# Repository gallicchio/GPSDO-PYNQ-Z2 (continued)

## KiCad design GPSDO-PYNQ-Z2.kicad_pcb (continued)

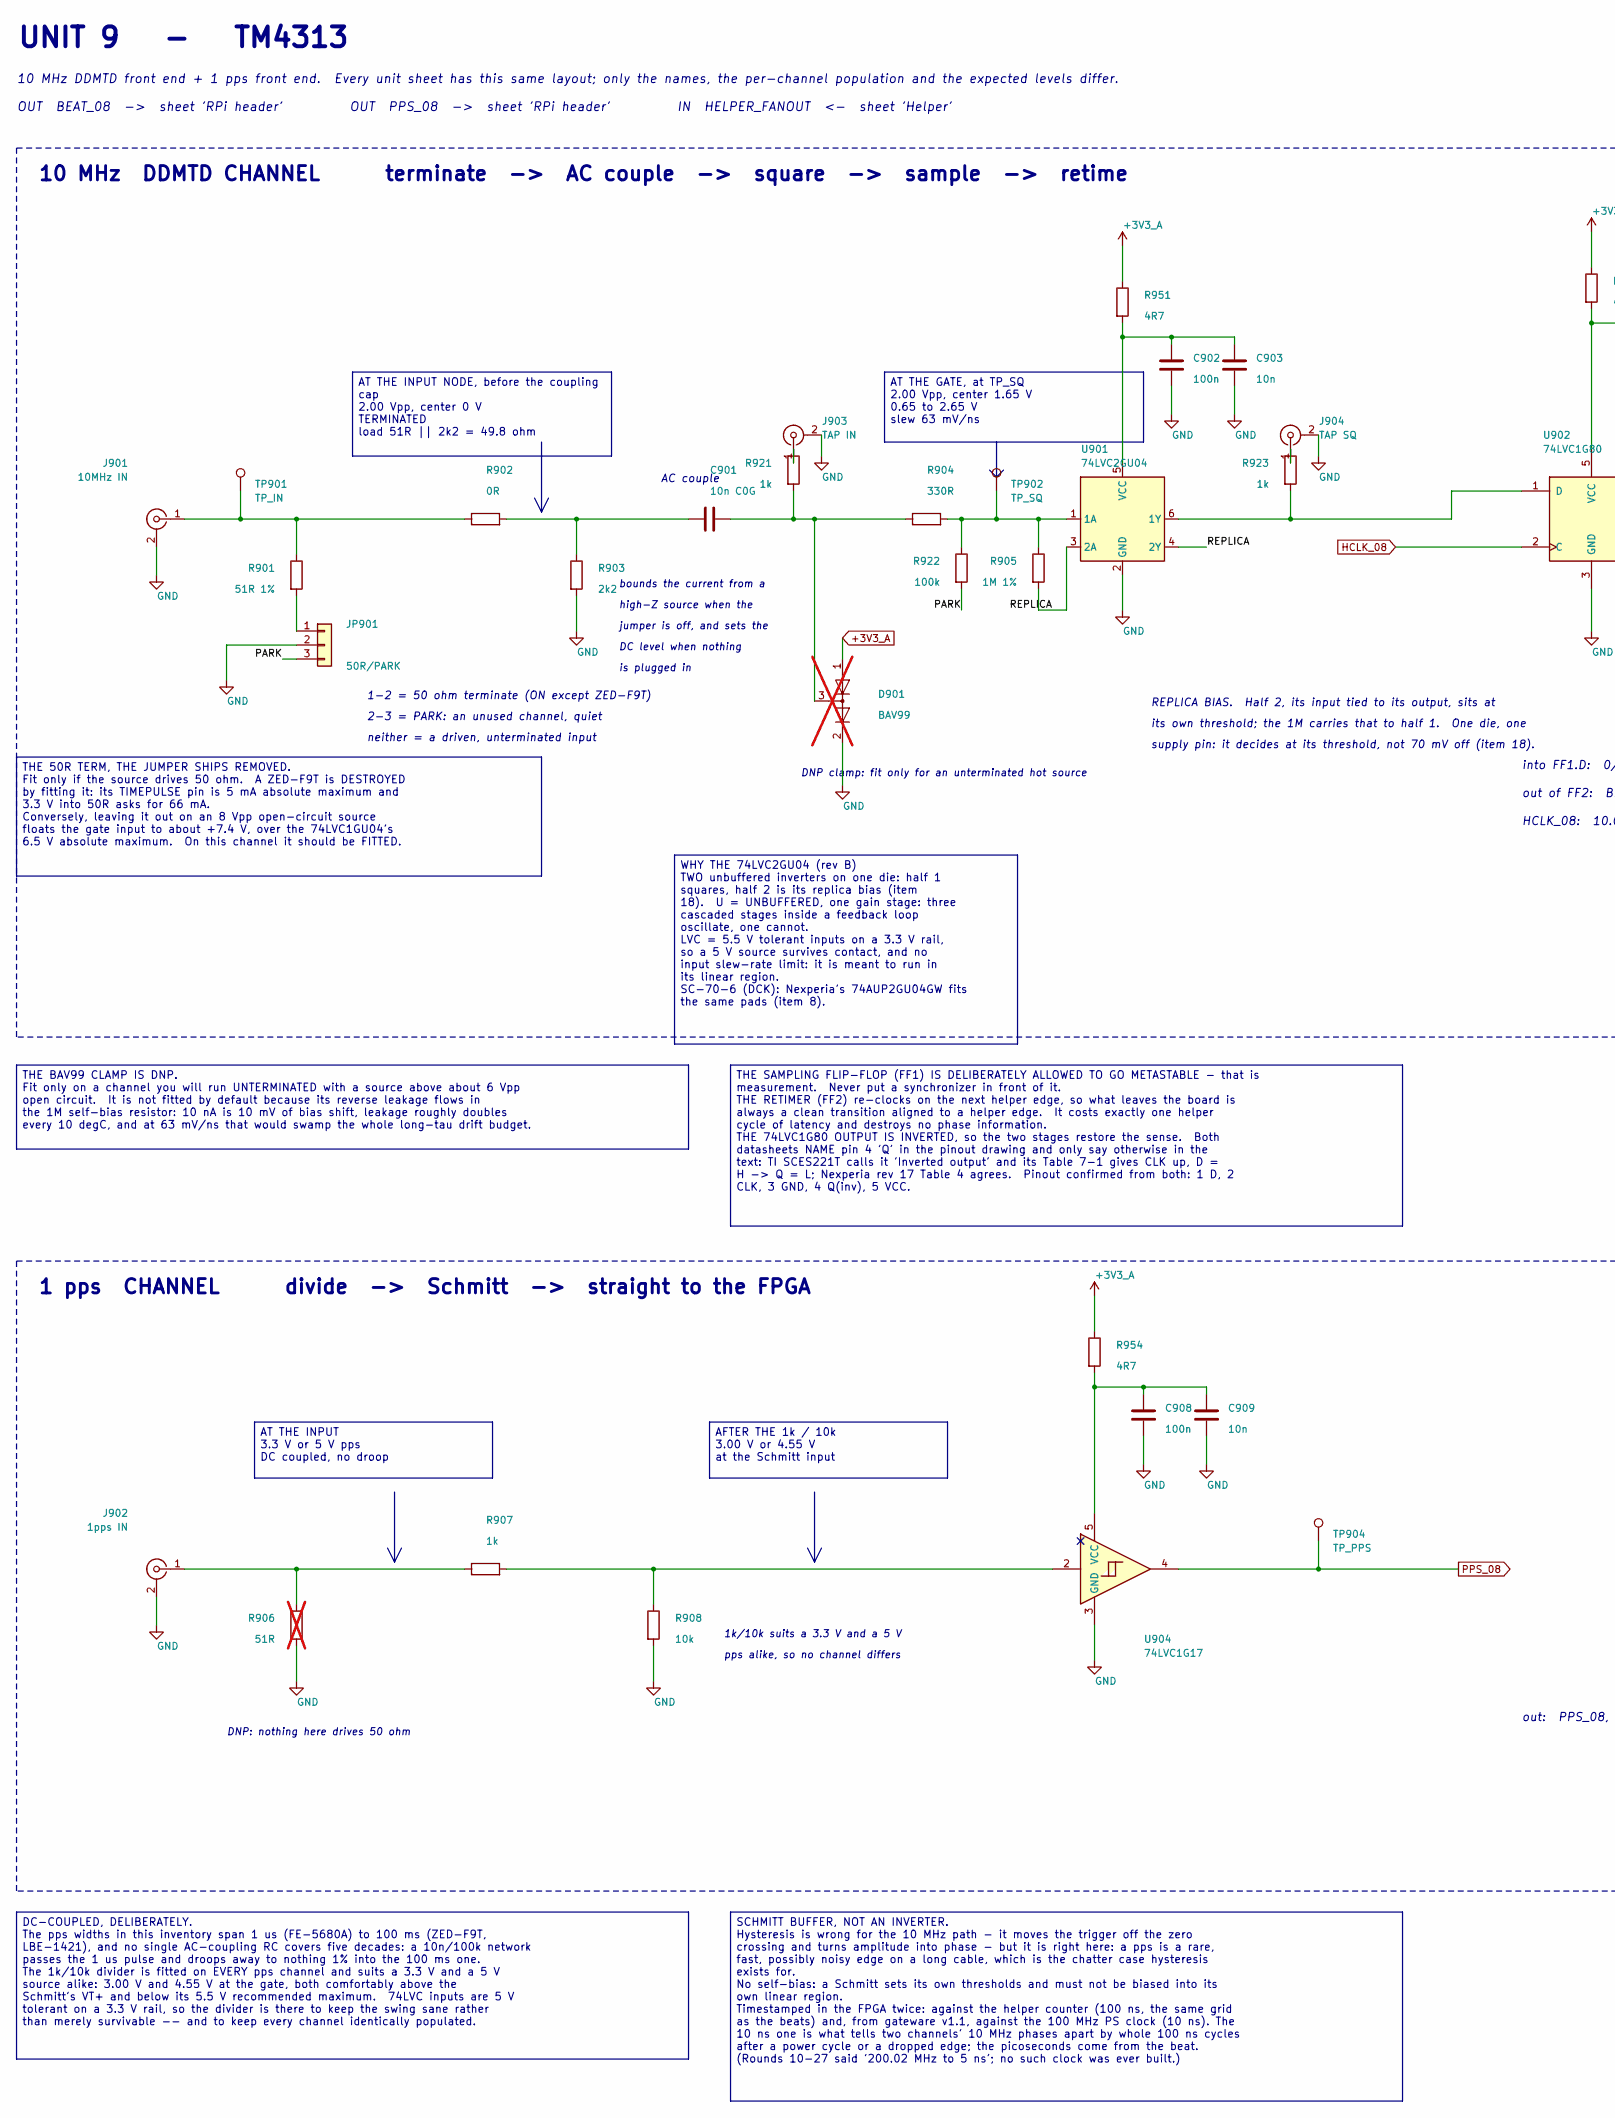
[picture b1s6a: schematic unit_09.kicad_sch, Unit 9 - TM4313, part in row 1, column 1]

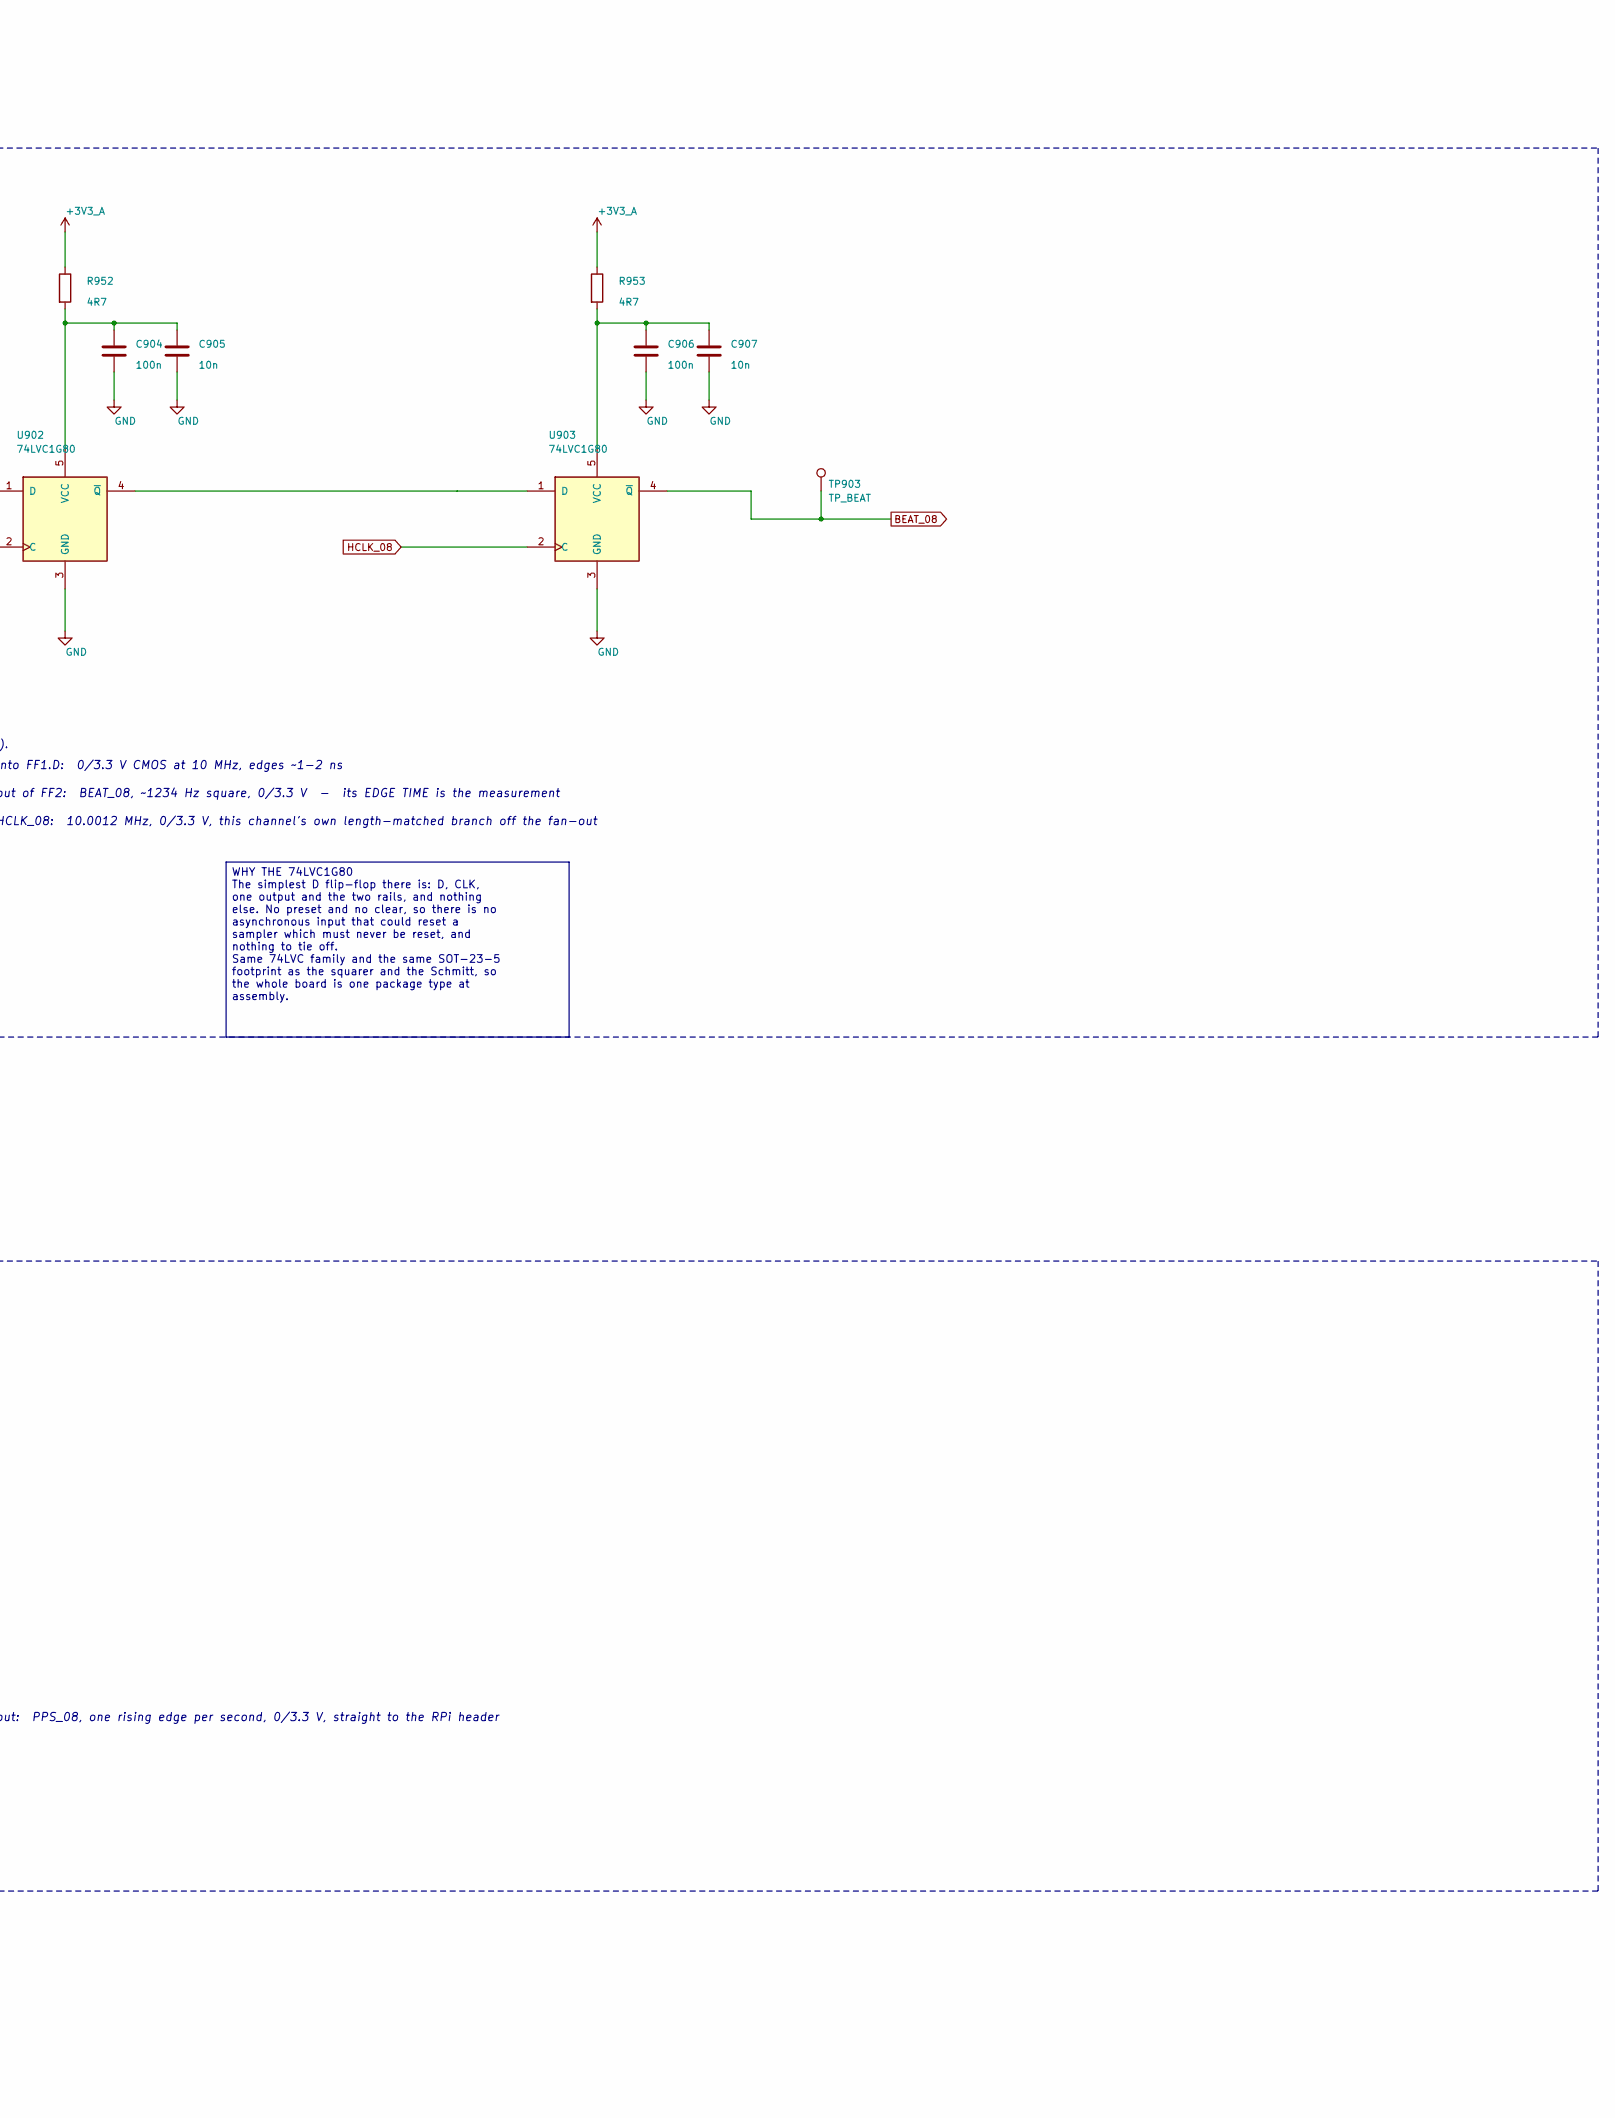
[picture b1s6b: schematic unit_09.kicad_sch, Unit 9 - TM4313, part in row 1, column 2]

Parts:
C901: 10n C0G; C_0805_2012Metric
C902, C904, C906, C908: 100n; C_0805_2012Metric
C903, C905, C907, C909: 10n; C_0805_2012Metric
D901: BAV99; SOT-23; LCSC C916421; not fitted
J901: 10MHz IN; SMA_Vertical_THT_Universal; LCSC C496549
J902: 1pps IN; SMA_Vertical_THT_Universal; LCSC C496549
J903: TAP IN; U.FL_Hirose_U.FL-R-SMT-1_Vertical; LCSC C88374
J904: TAP SQ; U.FL_Hirose_U.FL-R-SMT-1_Vertical; LCSC C88374
JP901: 50R/PARK; PinHeader_1x03_P2.54mm_Vertical
R901: 51R 1%; R_0805_2012Metric
R902: 0R; R_0805_2012Metric
R903: 2k2; R_0805_2012Metric
R904: 330R; R_0805_2012Metric
R905: 1M 1%; R_0805_2012Metric
R906: 51R; R_0805_2012Metric; not fitted
R907, R921, R923: 1k; R_0805_2012Metric
R908: 10k; R_0805_2012Metric
R922: 100k; R_0805_2012Metric
R951, R952, R953, R954: 4R7; R_0805_2012Metric
TP901: TP_IN; TestPoint_Pad_D1.5mm
TP902: TP_SQ; TestPoint_Pad_D1.5mm
TP903: TP_BEAT; TestPoint_Pad_D1.5mm
TP904: TP_PPS; TestPoint_Pad_D1.5mm
U901: 74LVC2GU04; SOT-363_SC-70-6; LCSC C116660
U902, U903: 74LVC1G80; SOT-23-5; LCSC C42879
U904: 74LVC1G17; SOT-23-5; LCSC C7836

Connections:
+3V3_A: D901.1 (K), R951.1, R952.1, R953.1, R954.1; also elsewhere on the board
/Unit 09/PARK: JP901.3, R922.2
/Unit 09/REPLICA: R905.2, U901.3 (2A), U901.4 (2Y)
BEAT_08: TP903.1, U903.4 (~Q); also elsewhere on the board
GND: C902.2, C903.2, C904.2, C905.2, C906.2, C907.2, C908.2, C909.2, D901.2 (A), J901.2 (Ext), J902.2 (Ext), J903.2 (Ext), J904.2 (Ext), JP901.2, R903.2, R906.2, R908.2, U901.2 (GND), U902.3 (GND), U903.3 (GND), U904.3 (GND); also elsewhere on the board
HCLK_08: U902.2 (C), U903.2 (C); also elsewhere on the board
unnamed: J901.1 (In), R901.1, R902.1, TP901.1
unnamed: J902.1 (In), R906.1, R907.1
unnamed: J903.1 (In), R921.1
unnamed: J904.1 (In), R923.1
unnamed: JP901.1, R901.2
unnamed: R907.2, R908.1, U904.2
unnamed: R904.2, R905.1, R922.1, TP902.1, U901.1 (1A)
unnamed: R923.2, U901.6 (1Y), U902.1 (D)
unnamed: C902.1, C903.1, R951.2, U901.5 (VCC)
unnamed: C904.1, C905.1, R952.2, U902.5 (VCC)
unnamed: U902.4 (~Q), U903.1 (D)
unnamed: C906.1, C907.1, R953.2, U903.5 (VCC)
unnamed: C908.1, C909.1, R954.2, U904.5 (VCC)
PPS_08: TP904.1, U904.4; also elsewhere on the board

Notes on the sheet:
UNIT 9 - TM4313
out of FF2: BEAT_08, ~1234 Hz square, 0/3.3 V - its EDGE TIME is the measurement
DNP: nothing here drives 50 ohm
bounds the current from a
supply pin: it decides at its threshold, not 70 mV off (item 18).
high-Z source when the
neither = a driven, unterminated input
1 pps CHANNEL divide -> Schmitt -> straight to the FPGA
is plugged in
10 MHz DDMTD front end + 1 pps front end. Every unit sheet has this same layout; only the names, the per-channel population and the expected levels differ.
pps alike, so no channel differs
OUT BEAT_08 -> sheet 'RPi header' OUT PPS_08 -> sheet 'RPi header' IN HELPER_FANOUT <- sheet 'Helper'
DNP clamp: fit only for an unterminated hot source
1-2 = 50 ohm terminate (ON except ZED-F9T)
DC level when nothing
HCLK_08: 10.0012 MHz, 0/3.3 V, this channel's own length-matched branch off the fan-out
jumper is off, and sets the
into FF1.D: 0/3.3 V CMOS at 10 MHz, edges ~1-2 ns
out: PPS_08, one rising edge per second, 0/3.3 V, straight to the RPi header
its own threshold; the 1M carries that to half 1. One die, one
1k/10k suits a 3.3 V and a 5 V
2-3 = PARK: an unused channel, quiet
AC couple
REPLICA BIAS. Half 2, its input tied to its output, sits at
10 MHz DDMTD CHANNEL terminate -> AC couple -> square -> sample -> retime
AFTER THE 1k / 10k 3.00 V or 4.55 V at the Schmitt input
THE SAMPLING FLIP-FLOP (FF1) IS DELIBERATELY ALLOWED TO GO METASTABLE - that is measurement. Never put a synchronizer in front of it. THE RETIMER (FF2) re-clocks on the next helper edge, so what leaves the board is always a clean transition aligned to a helper edge. It costs exactly one helper cycl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
AT THE INPUT 3.3 V or 5 V pps DC coupled, no droop
THE 50R TERM, THE JUMPER SHIPS REMOVED. Fit only if the source drives 50 ohm. A ZED-F9T is DESTROYED by fitting it: its TIMEPULSE pin is 5 mA absolute maximum and 3.3 V into 50R asks for 66 mA. Conversely, leaving it out on an 8 Vpp open-circuit source floats the gate input to about +7.4 V, over th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
DC-COUPLED, DELIBERATELY. The pps widths in this inventory span 1 us (FE-5680A) to 100 ms (ZED-F9T, LBE-1421), and no single AC-coupling RC covers five decades: a 10n/100k network passes the 1 us pulse and droops away to nothing 1% into the 100 ms one. The 1k/10k divider is fitted on EVERY pps chan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
WHY THE 74LVC2GU04 (rev B) TWO unbuffered inverters on one die: half 1 squares, half 2 is its replica bias (item 18). U = UNBUFFERED, one gain stage: three cascaded stages inside a feedback loop oscillate, one cannot. LVC = 5.5 V tolerant inputs on a 3.3 V rail, so a 5 V source survives contact, an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
WHY THE 74LVC1G80 The simplest D flip-flop there is: D, CLK, one output and the two rails, and nothing else. No preset and no clear, so there is no asynchronous input that could reset a sampler which must never be reset, and nothing to tie off. Same 74LVC family and the same SOT-23-5 footprint as t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
AT THE INPUT NODE, before the coupling cap 2.00 Vpp, center 0 V TERMINATED load 51R || 2k2 = 49.8 ohm
THE BAV99 CLAMP IS DNP. Fit only on a channel you will run UNTERMINATED with a source above about 6 Vpp open circuit. It is not fitted by default because its reverse leakage flows in the 1M self-bias resistor: 10 nA is 10 mV of bias shift, leakage roughly doubles every 10 degC, and at 63 mV/ns that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
SCHMITT BUFFER, NOT AN INVERTER. Hysteresis is wrong for the 10 MHz path - it moves the trigger off the zero crossing and turns amplitude into phase - but it is right here: a pps is a rare, fast, possibly noisy edge on a long cable, which is the chatter case hysteresis exists for. No self-bias: a S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
AT THE GATE, at TP_SQ 2.00 Vpp, center 1.65 V 0.65 to 2.65 V slew 63 mV/ns

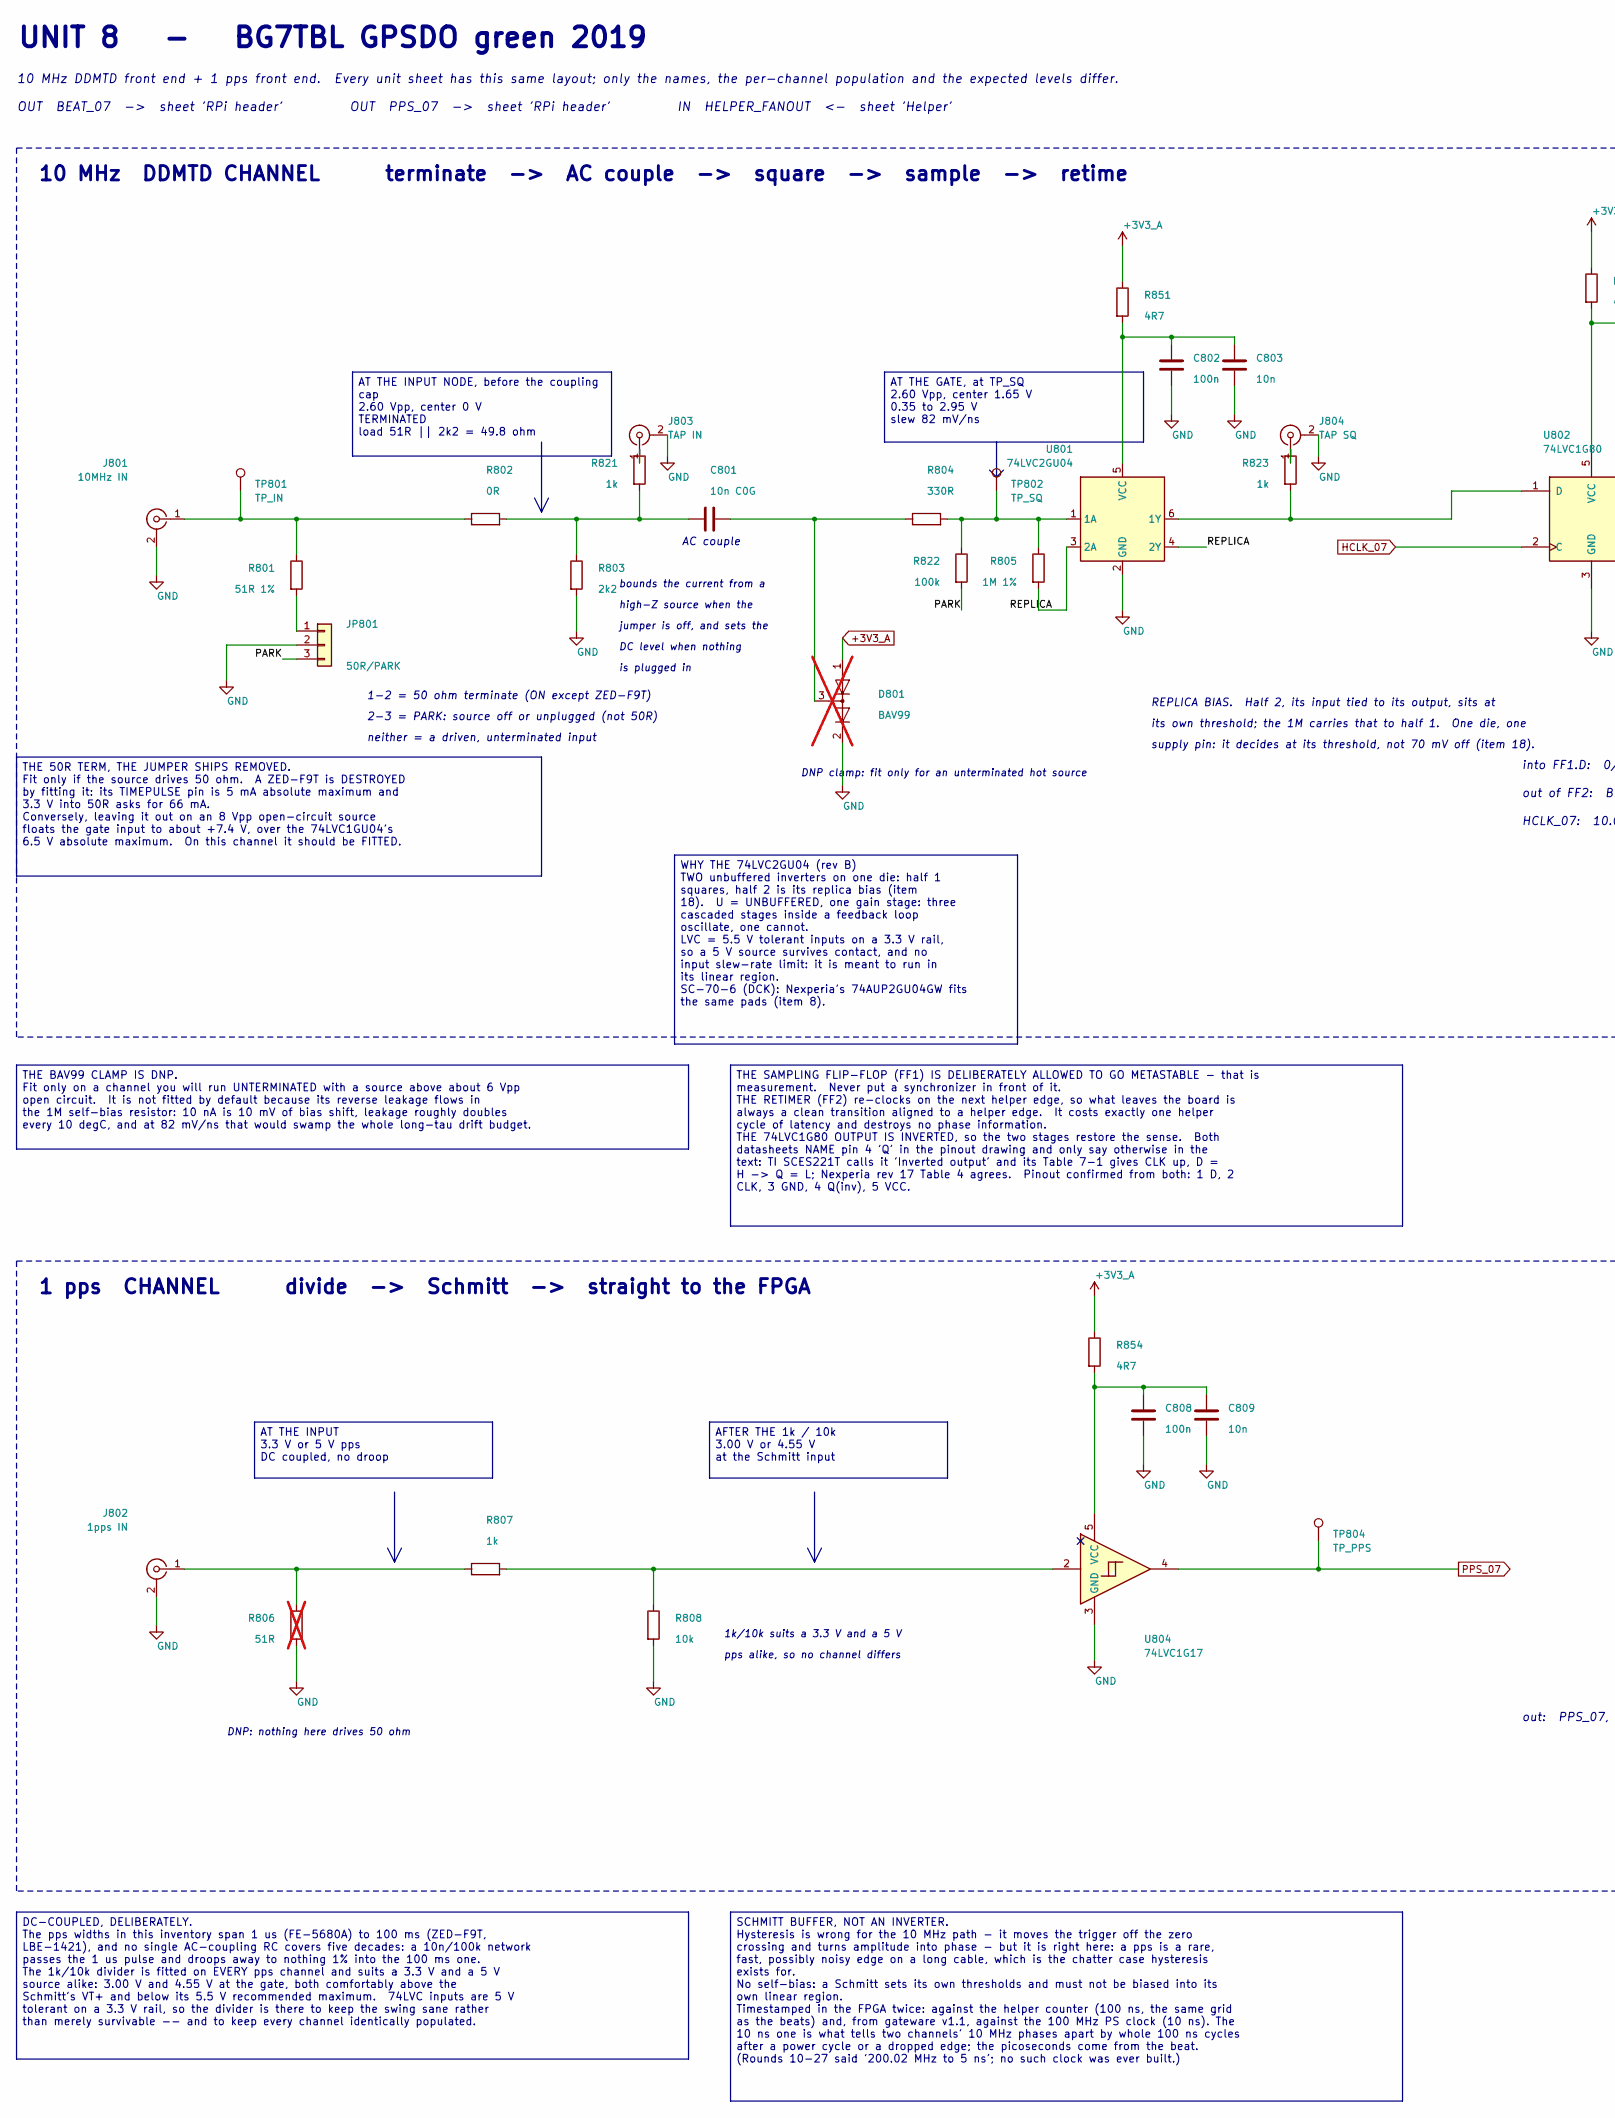
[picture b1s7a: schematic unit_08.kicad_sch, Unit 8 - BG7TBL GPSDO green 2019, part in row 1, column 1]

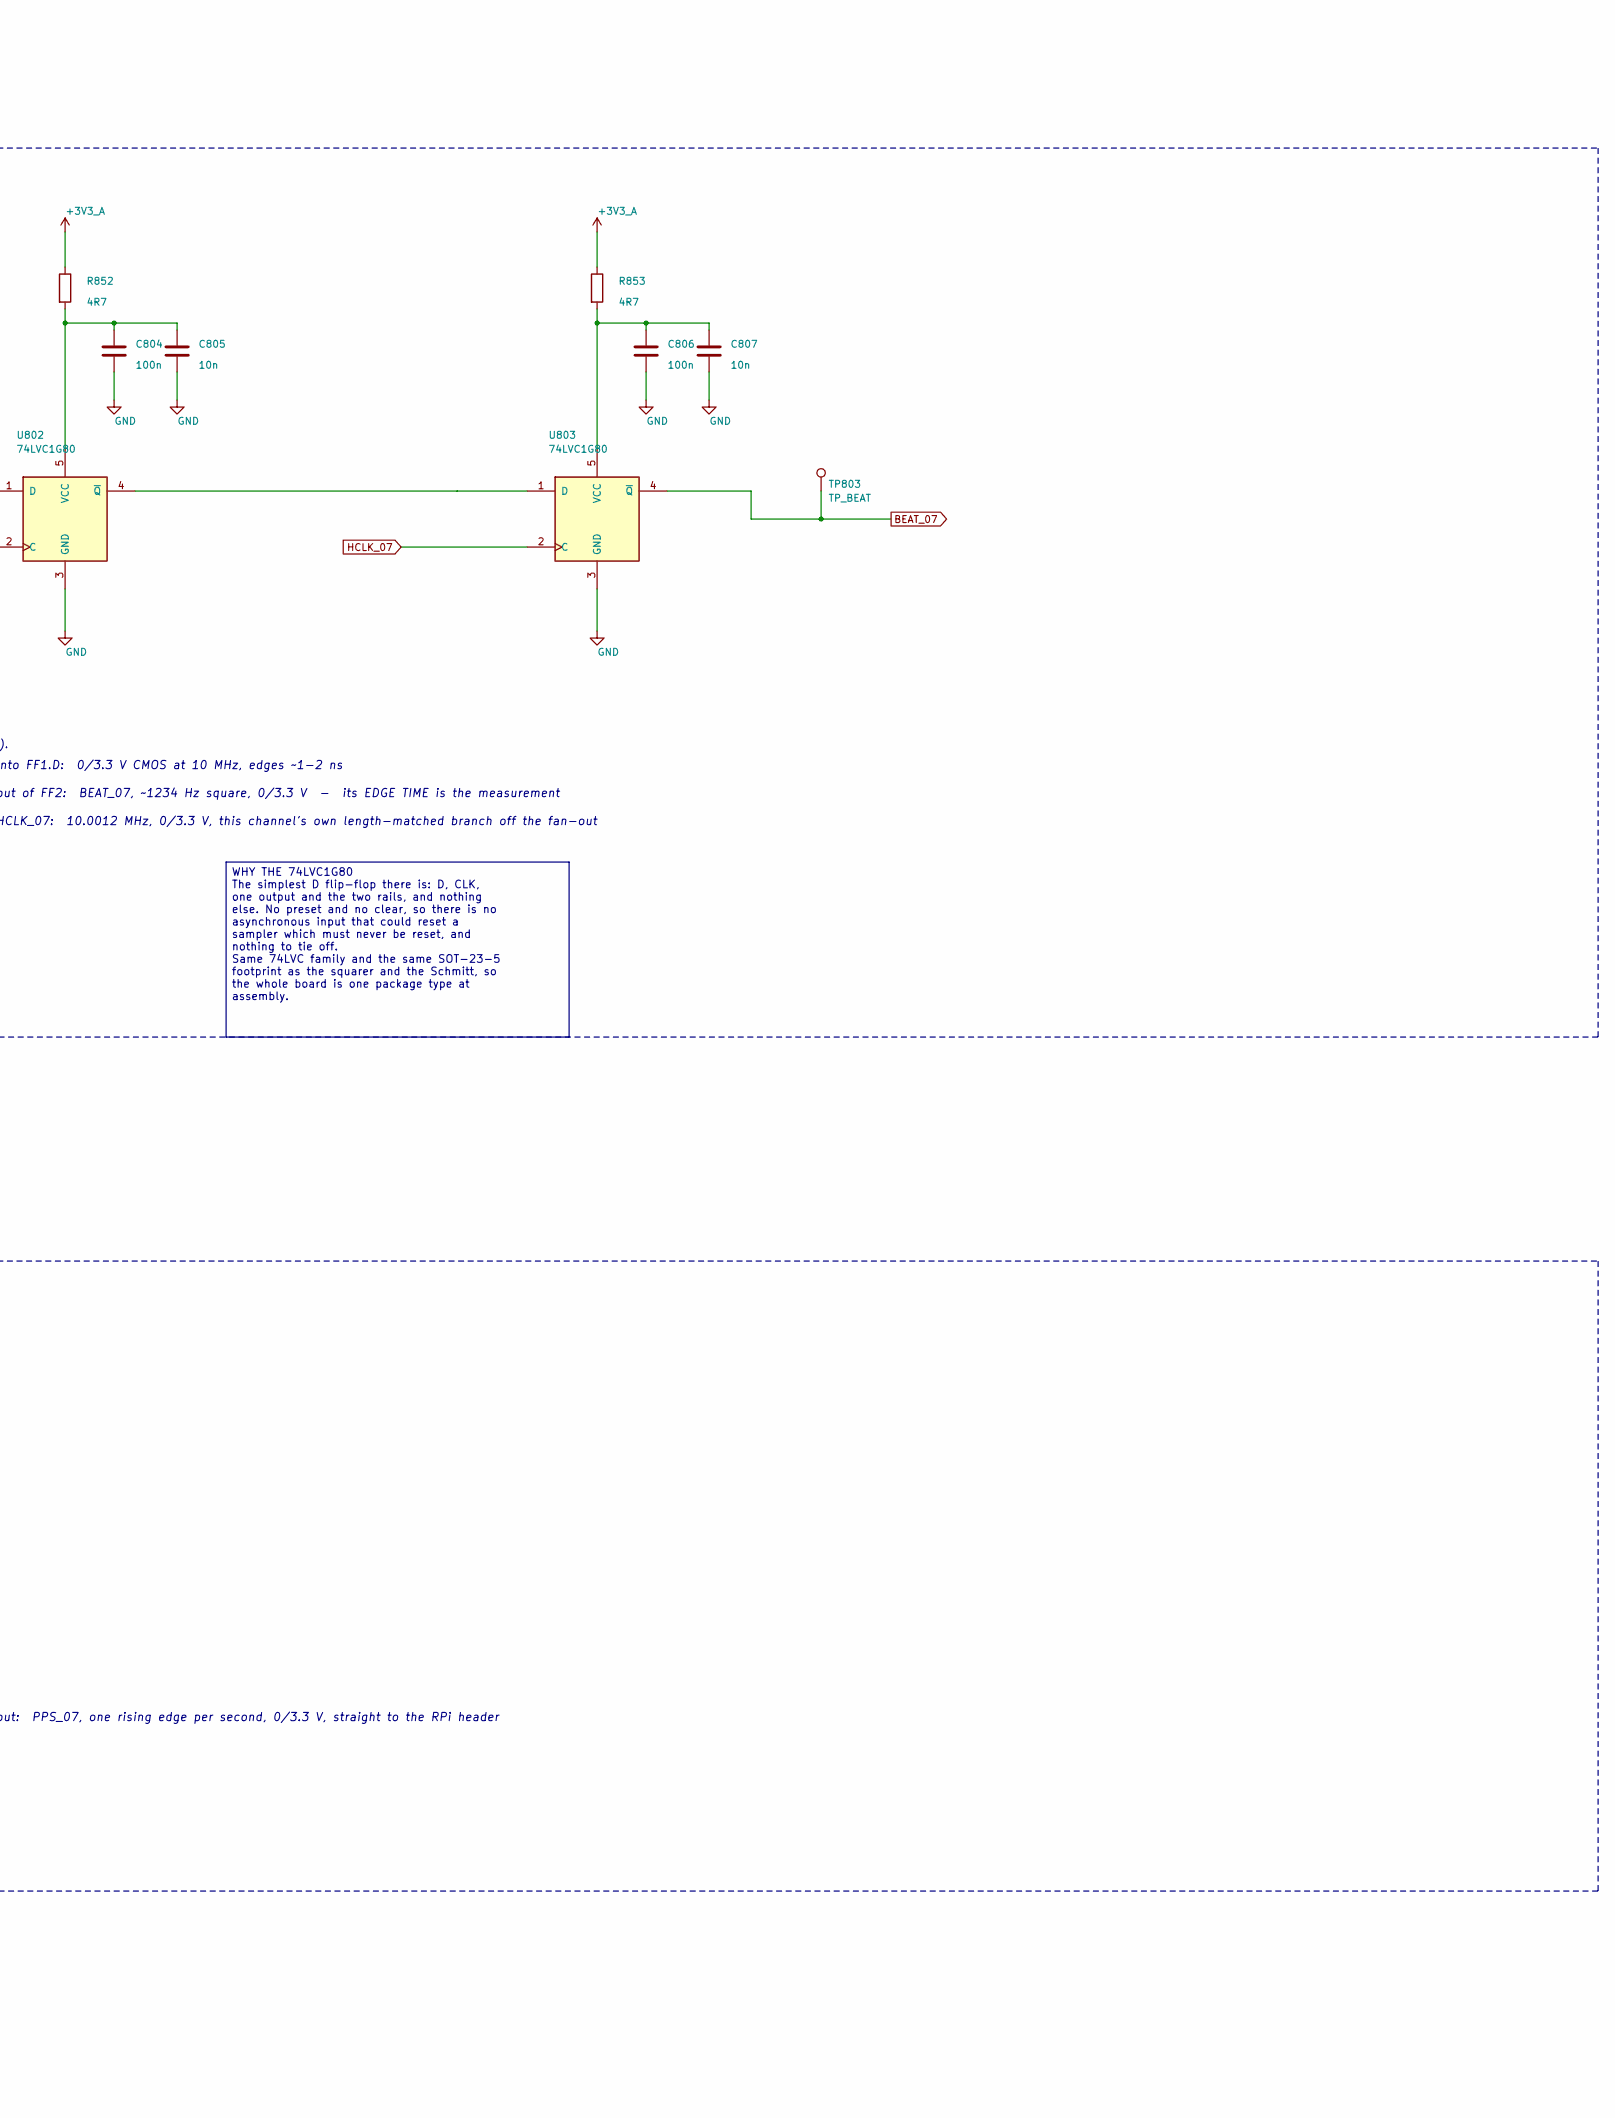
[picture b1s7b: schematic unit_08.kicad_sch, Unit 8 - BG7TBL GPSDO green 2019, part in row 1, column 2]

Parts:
C801: 10n C0G; C_0805_2012Metric
C802, C804, C806, C808: 100n; C_0805_2012Metric
C803, C805, C807, C809: 10n; C_0805_2012Metric
D801: BAV99; SOT-23; LCSC C916421; not fitted
J801: 10MHz IN; SMA_Vertical_THT_Universal; LCSC C496549
J802: 1pps IN; SMA_Vertical_THT_Universal; LCSC C496549
J803: TAP IN; U.FL_Hirose_U.FL-R-SMT-1_Vertical; LCSC C88374
J804: TAP SQ; U.FL_Hirose_U.FL-R-SMT-1_Vertical; LCSC C88374
JP801: 50R/PARK; PinHeader_1x03_P2.54mm_Vertical
R801: 51R 1%; R_0805_2012Metric
R802: 0R; R_0805_2012Metric
R803: 2k2; R_0805_2012Metric
R804: 330R; R_0805_2012Metric
R805: 1M 1%; R_0805_2012Metric
R806: 51R; R_0805_2012Metric; not fitted
R807, R821, R823: 1k; R_0805_2012Metric
R808: 10k; R_0805_2012Metric
R822: 100k; R_0805_2012Metric
R851, R852, R853, R854: 4R7; R_0805_2012Metric
TP801: TP_IN; TestPoint_Pad_D1.5mm
TP802: TP_SQ; TestPoint_Pad_D1.5mm
TP803: TP_BEAT; TestPoint_Pad_D1.5mm
TP804: TP_PPS; TestPoint_Pad_D1.5mm
U801: 74LVC2GU04; SOT-363_SC-70-6; LCSC C116660
U802, U803: 74LVC1G80; SOT-23-5; LCSC C42879
U804: 74LVC1G17; SOT-23-5; LCSC C7836

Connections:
+3V3_A: D801.1 (K), R851.1, R852.1, R853.1, R854.1; also elsewhere on the board
/Unit 08/PARK: JP801.3, R822.2
/Unit 08/REPLICA: R805.2, U801.3 (2A), U801.4 (2Y)
BEAT_07: TP803.1, U803.4 (~Q); also elsewhere on the board
GND: C802.2, C803.2, C804.2, C805.2, C806.2, C807.2, C808.2, C809.2, D801.2 (A), J801.2 (Ext), J802.2 (Ext), J803.2 (Ext), J804.2 (Ext), JP801.2, R803.2, R806.2, R808.2, U801.2 (GND), U802.3 (GND), U803.3 (GND), U804.3 (GND); also elsewhere on the board
HCLK_07: U802.2 (C), U803.2 (C); also elsewhere on the board
unnamed: C801.1, R802.2, R803.1, R821.2
unnamed: C801.2, D801.3 (K), R804.1
unnamed: J801.1 (In), R801.1, R802.1, TP801.1
unnamed: J802.1 (In), R806.1, R807.1
unnamed: J803.1 (In), R821.1
unnamed: J804.1 (In), R823.1
unnamed: JP801.1, R801.2
unnamed: R807.2, R808.1, U804.2
unnamed: R804.2, R805.1, R822.1, TP802.1, U801.1 (1A)
unnamed: R823.2, U801.6 (1Y), U802.1 (D)
unnamed: C802.1, C803.1, R851.2, U801.5 (VCC)
unnamed: C804.1, C805.1, R852.2, U802.5 (VCC)
unnamed: U802.4 (~Q), U803.1 (D)
unnamed: C806.1, C807.1, R853.2, U803.5 (VCC)
unnamed: C808.1, C809.1, R854.2, U804.5 (VCC)
PPS_07: TP804.1, U804.4; also elsewhere on the board

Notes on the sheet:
10 MHz DDMTD front end + 1 pps front end. Every unit sheet has this same layout; only the names, the per-channel population and the expected levels differ.
DNP: nothing here drives 50 ohm
2-3 = PARK: source off or unplugged (not 50R)
pps alike, so no channel differs
out: PPS_07, one rising edge per second, 0/3.3 V, straight to the RPi header
OUT BEAT_07 -> sheet 'RPi header' OUT PPS_07 -> sheet 'RPi header' IN HELPER_FANOUT <- sheet 'Helper'
REPLICA BIAS. Half 2, its input tied to its output, sits at
high-Z source when the
DC level when nothing
UNIT 8 - BG7TBL GPSDO green 2019
1k/10k suits a 3.3 V and a 5 V
10 MHz DDMTD CHANNEL terminate -> AC couple -> square -> sample -> retime
its own threshold; the 1M carries that to half 1. One die, one
1 pps CHANNEL divide -> Schmitt -> straight to the FPGA
bounds the current from a
1-2 = 50 ohm terminate (ON except ZED-F9T)
out of FF2: BEAT_07, ~1234 Hz square, 0/3.3 V - its EDGE TIME is the measurement
is plugged in
neither = a driven, unterminated input
AC couple
HCLK_07: 10.0012 MHz, 0/3.3 V, this channel's own length-matched branch off the fan-out
supply pin: it decides at its threshold, not 70 mV off (item 18).
jumper is off, and sets the
DNP clamp: fit only for an unterminated hot source
into FF1.D: 0/3.3 V CMOS at 10 MHz, edges ~1-2 ns
WHY THE 74LVC2GU04 (rev B) TWO unbuffered inverters on one die: half 1 squares, half 2 is its replica bias (item 18). U = UNBUFFERED, one gain stage: three cascaded stages inside a feedback loop oscillate, one cannot. LVC = 5.5 V tolerant inputs on a 3.3 V rail, so a 5 V source survives contact, an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
AFTER THE 1k / 10k 3.00 V or 4.55 V at the Schmitt input
SCHMITT BUFFER, NOT AN INVERTER. Hysteresis is wrong for the 10 MHz path - it moves the trigger off the zero crossing and turns amplitude into phase - but it is right here: a pps is a rare, fast, possibly noisy edge on a long cable, which is the chatter case hysteresis exists for. No self-bias: a S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
AT THE GATE, at TP_SQ 2.60 Vpp, center 1.65 V 0.35 to 2.95 V slew 82 mV/ns
WHY THE 74LVC1G80 The simplest D flip-flop there is: D, CLK, one output and the two rails, and nothing else. No preset and no clear, so there is no asynchronous input that could reset a sampler which must never be reset, and nothing to tie off. Same 74LVC family and the same SOT-23-5 footprint as t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
DC-COUPLED, DELIBERATELY. The pps widths in this inventory span 1 us (FE-5680A) to 100 ms (ZED-F9T, LBE-1421), and no single AC-coupling RC covers five decades: a 10n/100k network passes the 1 us pulse and droops away to nothing 1% into the 100 ms one. The 1k/10k divider is fitted on EVERY pps chan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
THE BAV99 CLAMP IS DNP. Fit only on a channel you will run UNTERMINATED with a source above about 6 Vpp open circuit. It is not fitted by default because its reverse leakage flows in the 1M self-bias resistor: 10 nA is 10 mV of bias shift, leakage roughly doubles every 10 degC, and at 82 mV/ns that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
AT THE INPUT 3.3 V or 5 V pps DC coupled, no droop
THE SAMPLING FLIP-FLOP (FF1) IS DELIBERATELY ALLOWED TO GO METASTABLE - that is measurement. Never put a synchronizer in front of it. THE RETIMER (FF2) re-clocks on the next helper edge, so what leaves the board is always a clean transition aligned to a helper edge. It costs exactly one helper cycl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
AT THE INPUT NODE, before the coupling cap 2.60 Vpp, center 0 V TERMINATED load 51R || 2k2 = 49.8 ohm
THE 50R TERM, THE JUMPER SHIPS REMOVED. Fit only if the source drives 50 ohm. A ZED-F9T is DESTROYED by fitting it: its TIMEPULSE pin is 5 mA absolute maximum and 3.3 V into 50R asks for 66 mA. Conversely, leaving it out on an 8 Vpp open-circuit source floats the gate input to about +7.4 V, over th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
